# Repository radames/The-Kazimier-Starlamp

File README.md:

# Startlamp 

## PCB with modules

* ESP8266 Wemos D1 mini
* DFPLayer mini MP3
* AMS1117 3.3V
* PWM-FET
* MP1584EN DC-DC
* RTC DS3231

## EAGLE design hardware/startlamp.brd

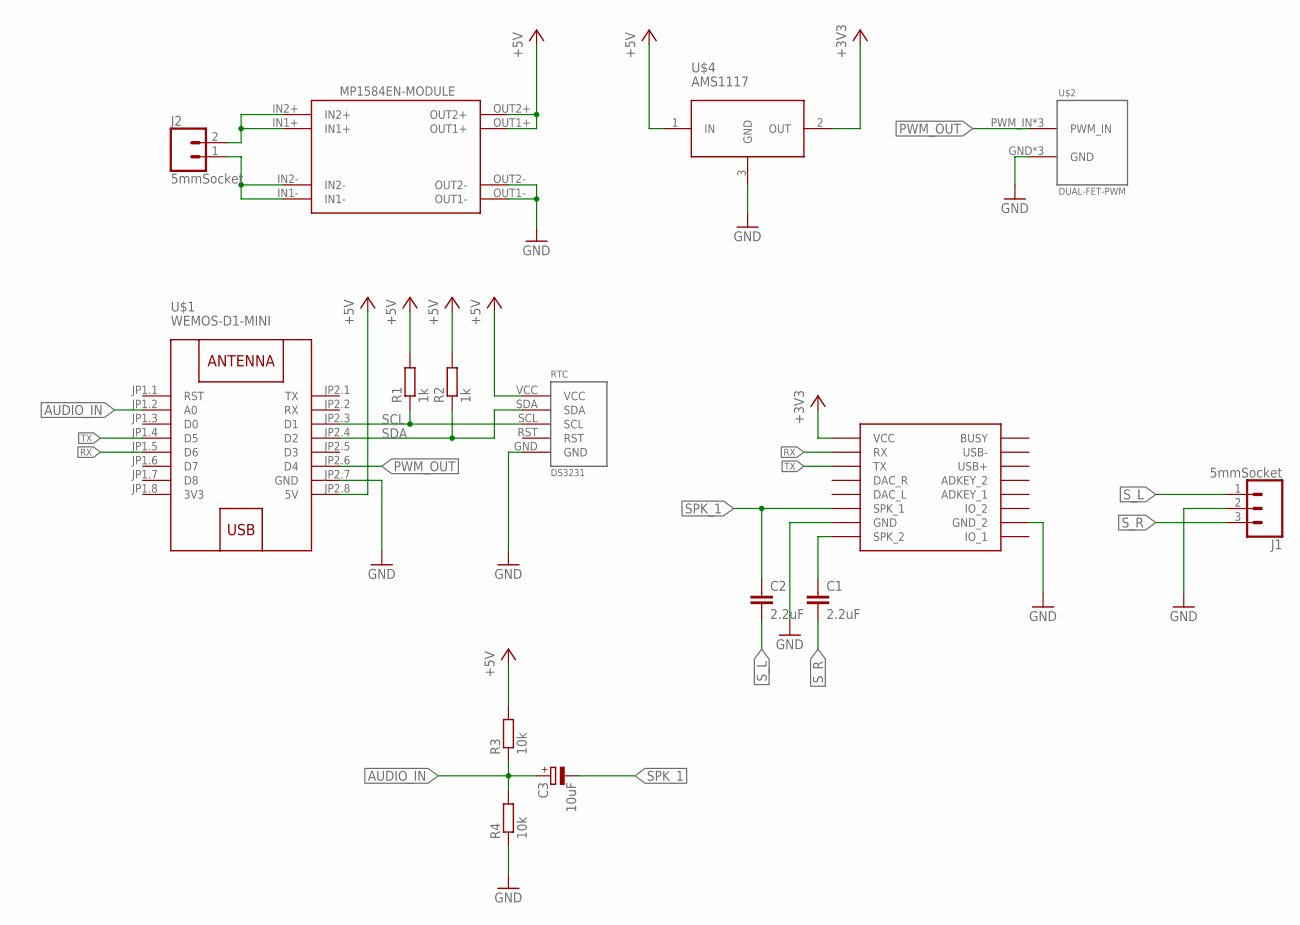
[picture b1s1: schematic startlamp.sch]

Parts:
C1, C2: 2.2uF; C050-024X044
C3: 10uF; E5-4
J1: 5mmSocket; SCREWTERMINAL-5MM-3
J2: 5mmSocket; SCREWTERMINAL-5MM-2
R1, R2: 1k; 0204V
R3, R4: 10k; 0204V
RTC: DS3231; RTC-MINI
U1: MP1584; DSUN_NEW
U$1: WEMOS-D1-MINI
U$2: DUAL-FET-PWM
U$3: DFPLAYER
U$4: AMS1117; REG-AMS1117-3P#V

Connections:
3V3: U$1.JP1.8 (3V3)
+3V3: U$3.VCC, U$4.2 (OUT)
+5V: R1.2, R2.2, R3.2, RTC.VCC, U1.OUT1+, U1.OUT2+, U$1.JP2.8 (5V), U$4.1 (IN)
AUDIO_IN: C3.+, R3.1, R4.2, U$1.JP1.2 (A0)
GND: J1.2, R4.1, RTC.GND, U1.OUT1-, U1.OUT2-, U$1.JP2.7 (GND), U$2.GND, U$2.GND2 (GND), U$2.GND3 (GND), U$3.GND, U$3.GND_2, U$4.3 (GND)
IN+: J2.2, U1.IN1+, U1.IN2+
IN-: J2.1, U1.IN1-, U1.IN2-
PWM_OUT: U$1.JP2.6 (D4), U$2.PWM_IN, U$2.PWM_IN2 (PWM_IN), U$2.PWM_IN3 (PWM_IN)
RX: U$1.JP1.5 (D6), U$3.RX
SCL: R1.1, RTC.SCL, U$1.JP2.3 (D1)
SDA: R2.1, RTC.SDA, U$1.JP2.4 (D2)
SPK_1: C2.1, C3.-, U$3.SPK1 (SPK_1)
SPK_2: C1.1, U$3.SPK2 (SPK_2)
S_L: C2.2, J1.1
S_R: C1.2, J1.3
TX: U$1.JP1.4 (D5), U$3.TX

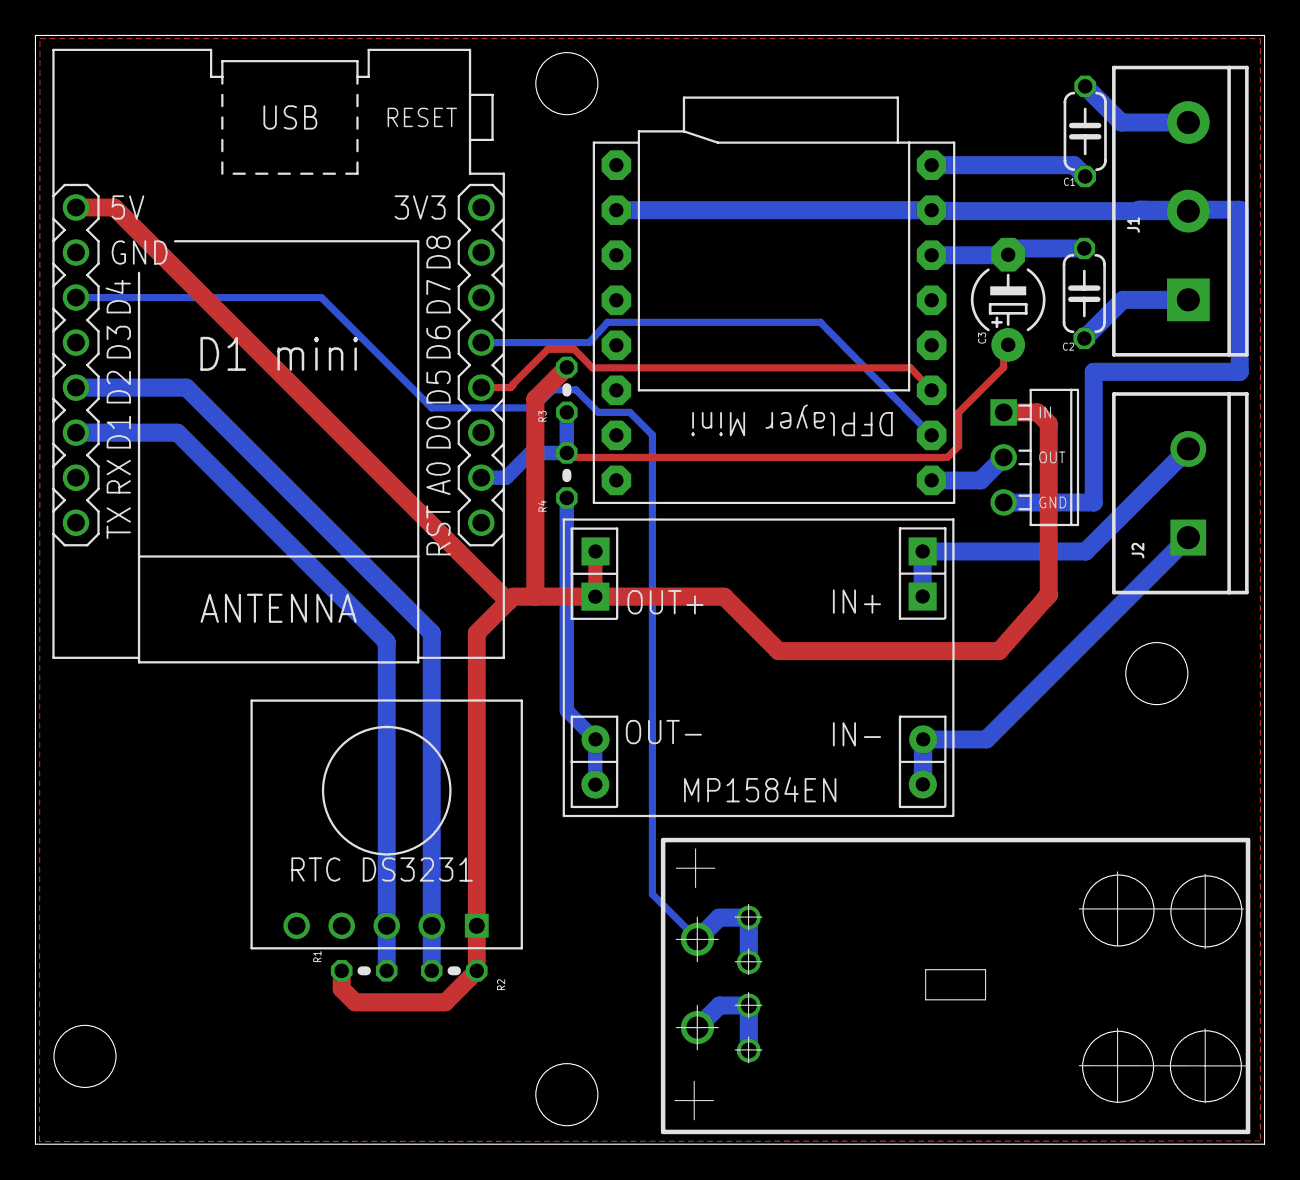
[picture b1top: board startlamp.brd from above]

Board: 2 copper layers, 69.3 x 62.5 mm, 15 parts (0 on the bottom side), 15 nets.

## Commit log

2017-10-18 electronics design source files
2017-10-23 Test code for pcb and modules
2017-10-24 pcb board image added
2017-10-26 first scheduler sketch
2017-10-27 Organizing classes for AudioAnalysis and MP3 PLayer
2017-10-28 time conversion functions on scheduler
    first sketch of the event scheduler
2017-10-28 loop and stop on mp3 class
2017-10-29 format time print log
2017-10-29 keep track of play or stop mp3 status
2017-10-29 sine wave patter for LED on ambient mode
2017-10-29 parameter for led max pwm
2017-10-29 first scheduler draft with callback returning event id
2017-10-29 events callback with state time length and id
2017-10-29 fix audio track ids
2017-10-29 scheduler working for periods and time length
2017-10-30 state machine for event update
2017-10-30 fix mp3 id change to prefix increments
2017-10-31 cryptic unsynchronous error fixed for ds3231 com with arduino
2017-10-31 remove parameters.h from repository
    added parameters.h config as example
2017-10-31 new parameters added to config file
2017-10-31 parameters for events moved to config file
2017-10-31 make scheduler work only on start/end time
2017-10-31 check periods from the past, make scheduler work only on future periods
2017-10-31 change position for main state machine events
2017-10-31 enable event2 and make sure if are on closed brackets
2017-10-31 enable debug mode log time but mess with audio analysis
2017-10-31 adding another parameter to config file
2017-10-31 extra debug macro variable
2017-10-31 reset AudioAnalysis parameters
2017-11-01 scheduler start/end on the state machine
    start and end for overall scheduler working now
2017-11-01 force play sounds on debug mode startup
2017-11-02 log send track play commands
2017-11-02 fix includes
2017-11-02 added error checking for mp3 module
    check for errors in the communication with the mp3 module, forces to try
    again in the next interaction
2017-11-02 simple version of the light player
2017-11-02 check errors for other mp3 commands
2017-11-04 reset play state
2017-11-04 fix events start time to work prior to scheduler start
2017-11-07 ambient mode with or without sound, made ambient light mode default
2017-11-07 ambient mode stays on ambiente mode
2017-11-07 macro to enable/disable ambient mode
2017-11-07 fix unsigned operations, new parameter on config file

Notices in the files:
parts and their libraries:
SparkFun-Connectors: Licensing: Creative Commons ShareAlike 4.0 International - https://creativecommons.org/licenses/by-sa/4.0
